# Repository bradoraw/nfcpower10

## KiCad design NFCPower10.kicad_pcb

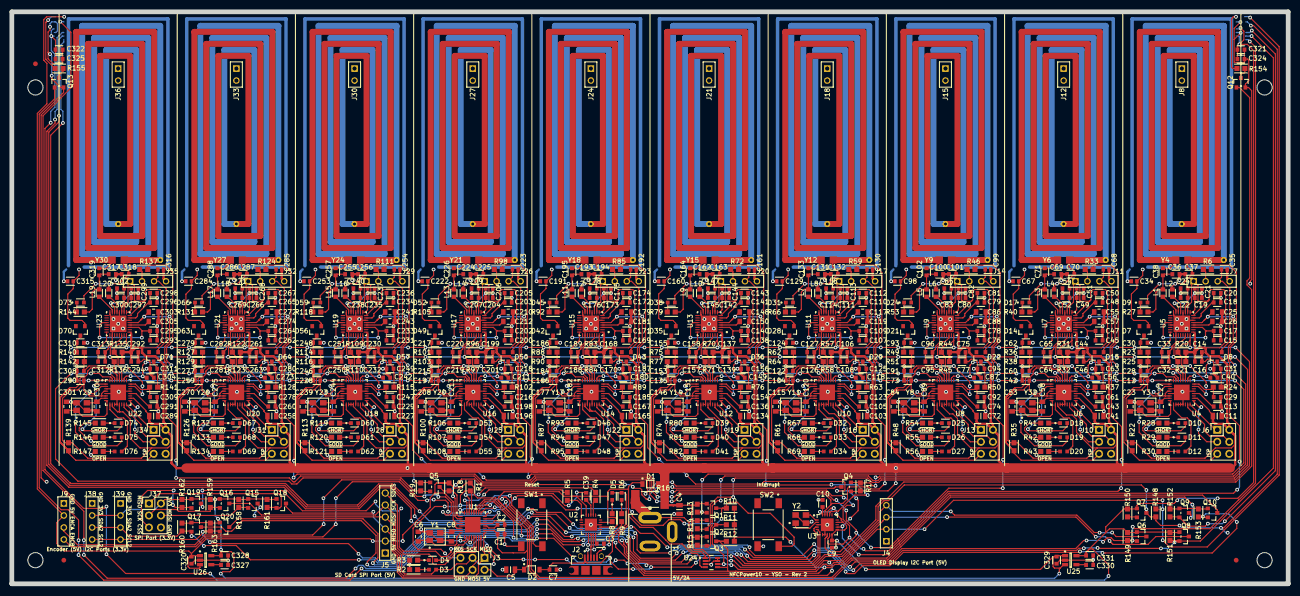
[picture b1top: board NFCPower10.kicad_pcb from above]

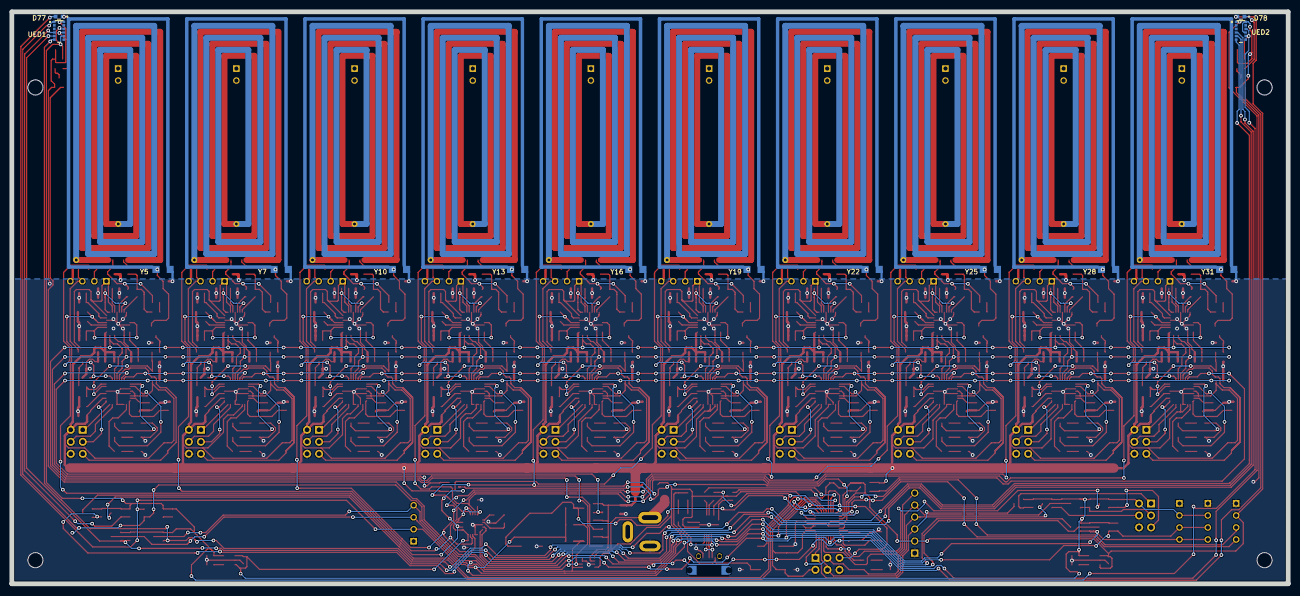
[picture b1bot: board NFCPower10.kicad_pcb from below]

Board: 2 copper layers, 270.0 x 121.0 mm, 666 parts (14 on the bottom side), 410 nets.

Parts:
C1, C2, C3, C7, C9, C10, C12, C13, C39, C42, C43, C73, C74, C104, C105, C135, C136, C166, C167, C197, C198, C228, C229, C259, C260, C290, C291, C321, C322, C327, C330: CC0603KPX7R9BB104; YAGEO-CC0603-0-0-0
C4, C5, C11, C41, C72, C103, C134, C165, C196, C227, C258, C289: CC0805ZKY5V6BB106; YAGEO-CC0805-0-0-0
C6, C8, C23, C25, C26, C27, C53, C55, C57, C58, C84, C86, C88, C89, C115, C117, C119, C120, C146, C148, C150, C151, C177, C179, C181, C182, C208, C210, C212, C213, C239, C241, C243, C244, C270, C272, C274, C275, C301, C303, C305, C306: CGA3E2C0G1H060D080AA; TDK-CGA3E-0.3-0.1-0-0-IPC_A
C14, C15, C18, C19, C22, C32, C44, C45, C48, C49, C52, C64, C75, C76, C79, C80, C83, C95, C106, C107, C110, C111, C114, C126, C137, C138, C141, C142, C145, C157, C168, C169, C172, C173, C176, C188, C199, C200, C203, C204, C207, C219, C230, C231, C234, C235, C238, C250, C261, C262, C265, C266, C269, C281, C292, C293, C296, C297, C300, C312, C320, C324, C325, C328, C329, C331: CC0603MRX5R5BB225; YAGEO-CC0603-0-0-0
C16, C17, C20, C21, C24, C33, C46, C47, C50, C51, C54, C65, C77, C78, C81, C82, C85, C96, C108, C109, C112, C113, C116, C127, C139, C140, C143, C144, C147, C158, C170, C171, C174, C175, C178, C189, C201, C202, C205, C206, C209, C220, C232, C233, C236, C237, C240, C251, C263, C264, C267, C268, C271, C282, C294, C295, C298, C299, C302, C313: CC0603KRX7R9BB103; YAGEO-CC0603-0-0-0
C28, C60, C91, C122, C153, C184, C215, C246, C277, C308: CC0603KRX7R6BB224; YAGEO-CC0603-0-0-0
C29, C40, C56, C61, C87, C92, C118, C123, C149, C154, C180, C185, C211, C216, C242, C247, C273, C278, C304, C309: CC0603KRX7R7BB105; YAGEO-CC0603-0-0-0
C30, C31, C36, C37, C62, C63, C69, C70, C93, C94, C100, C101, C124, C125, C131, C132, C155, C156, C162, C163, C186, C187, C193, C194, C217, C218, C224, C225, C248, C249, C255, C256, C279, C280, C286, C287, C310, C311, C317, C318: CC0603KRX7R9BB102; YAGEO-CC0603-0-0-0
C34, C35, C67, C68, C98, C99, C129, C130, C160, C161, C191, C192, C222, C223, C253, C254, C284, C285, C315, C316: C0603C209C5GACTU; KEMET-C0603C-CF-0-0-MFG
C38, C71, C102, C133, C164, C195, C226, C257, C288, C319: CC0603KRX7R9BB181; YAGEO-CC0603-0-0-0
D1, D2: BAT54T1G; On_Semiconductor-BAT54T1G-Manufacturer_Recommended
D3, D12, D20, D27, D34, D41, D48, D55, D62, D69, D76: LTST-C190TBKT; Vishay_Lite-On-LTST-C190TBKT-Manufacturer_Recommended
D4, D10, D18, D25, D32, D39, D46, D53, D60, D67, D74: LTST-C190KRKT; Lite-On-LTST-C190KRKT-MFG
D5, D11, D19, D26, D33, D40, D47, D54, D61, D68, D75, D77, D78: LTST-C190KGKT; Lite-On-LTST-C190KGKT-MFG
D6, D9, D17, D24, D31, D38, D45, D52, D59, D66, D73: LTST-C190KSKT; Lite-On-LTST-C190KSKT-MFG
D7, D8, D14, D15, D21, D22, D28, D29, D35, D36, D42, D43, D49, D50, D56, D57, D63, D64, D70, D71: BAS40-7-F; Diodes_Inc.-SOT23-01_2017-0-MFG
FID1, FID2, FID3: fiducial; Fiducial_1mm_Dia_2.54mm_Outer_CopperTop
J1: PJ-002AH; CUI_PJ-002AH
J2: 475890001; Molex-475890001-MFG
J3, J6, J10, J13, J16, J19, J22, J25, J28, J31, J34, J37: Conn_02x03_Odd_Even; Pin_Header_Straight_2x03_Pitch2.54mm
J4, J7, J9, J11, J14, J17, J20, J23, J26, J29, J32, J35, J38, J39: SSW-104-01-T-S; Samtec-SSW-104-01-T-S-Manufacturer_Recommended
J5: SSW-106-02-T-S; Samtec-SSW-106-02-T-S-Manufacturer_Recommended
J8, J12, J15, J18, J21, J24, J27, J30, J33, J36: SSW-102-01-T-S; Samtec-SSW-102-01-T-S-Manufacturer_Recommended
L1, L2, L3, L4, L5, L6, L7, L8, L9, L10, L11, L12, L13, L14, L15, L16, L17, L18, L19, L20: MLJ1608WR27JT000; INDC1608X95N
MT1, MT2, MT3, MT4: Mount Hole M3; MountingHole_3.2mm_M3
Q1, Q2, Q3, Q4, Q5, Q6, Q7, Q8, Q9, Q10, Q12, Q13, Q15, Q16, Q17, Q18, Q19, Q20: BSS138; ON_Semiconductor-318-08-01_2018-AS-MFG
R1, R10, R13, R14, R15, R17, R18, R19, R20, R21, R22, R23, R25, R31, R32, R35, R36, R38, R44, R45, R48, R49, R51, R57, R58, R61, R62, R64, R70, R71, R74, R75, R77, R83, R84, R87, R88, R90, R96, R97, R100, R101, R103, R109, R110, R113, R114, R116, R122, R123, R126, R127, R129, R135, R136, R139, R140, R142, R148, R150, R152, R153: RC0603FR-0710KL; Yageo-RC0603-0-0-IPC_A
R2, R3, R4, R5, R6, R8, R9, R11, R12, R24, R27, R28, R29, R30, R33, R37, R40, R41, R42, R43, R46, R50, R53, R54, R55, R56, R59, R63, R66, R67, R68, R69, R72, R76, R79, R80, R81, R82, R85, R89, R92, R93, R94, R95, R98, R102, R105, R106, R107, R108, R111, R115, R118, R119, R120, R121, R124, R128, R131, R132, R133, R134, R137, R141, R144, R145, R146, R147, R149, R151, R154, R155, R158, R159, R160, R161, R162, R163: RC0603FR-071K65L; Yageo-RC0603-0-0-IPC_A
R16: RL2512FK-070R1L; YAGEO-RL2512-02_2018-10-MFG
SW1, SW2: FSM2JSMAA; TE_Connectivity-FSM2JSMAA-MFG
U1, U4, U6, U8, U10, U12, U14, U16, U18, U20, U22: ATMEGA328P-MU; Microchip___Atmel-ATMEGA328P-MU-Level_A
U2: FT231XQ-R; FTDI-QFN-20-0-0-MFG
U3: Si5351A-B-GM; Silicon_Labs-Si5351A-B-GM-Level_A
U5, U7, U9, U11, U13, U15, U17, U19, U21, U23: ST25R3916-AQWT; STMicroelectronics-VFQFPN32-B04R-0-1-IPC_A
U24: INA219AIDCNR; Texas_Instruments-DCN0008A-0-0-MFG
U25: LP3985IM5X-2.8_NOPB; TI_National_Semiconductor-LP3985IM5X-2.8_NOPB-Level_A
U26: LP3985IM5X-3.3_NOPB; TI_National_Semiconductor-LP3985IM5X-3.3_NOPB-Level_A
UED1, UED2: VL6180XV0NR_1; STMicroelectronics-VL6180XV0NR_1-MFG
Y1, Y3, Y8, Y11, Y14, Y17, Y20, Y23, Y26, Y29, Y32: TSX-3225_16.0000MF09Z-AC3; Epson-TSX-3225_16.0000MF09Z-AC3-0
Y2: ABM8G-25.000MHz-B4Y-T; Abracon-ABM8G-25.000MHz-B4Y-T-0
Y4, Y6, Y9, Y12, Y15, Y18, Y21, Y24, Y27, Y30: Coil_49_18_6T_2Layer
Y5, Y7, Y10, Y13, Y16, Y19, Y22, Y25, Y28, Y31: Field_Sensor_54_22

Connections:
+5V: C1.1, C5.2, C320.1, D1.1, D2.1, D77.2, D78.2, J3.2, J4.2, J5.2, J9.2, R1.1, R10.1, R11.1, R12.1, R18.1, R148.1, U1.4, U1.6, U1.18, U2.12, U2.20, U24.4, U26.1, U26.3
+5VP: C4.2, C11.2, C12.1, C14.1, C16.1, C41.2, C42.1, C44.1, C46.1, C72.2, C73.1, C75.1, C77.1, C103.2, C104.1, C106.1, C108.1, C134.2, C135.1, C137.1, C139.1, C165.2, C166.1, C168.1, C170.1, C196.2, C197.1, C199.1, C201.1, C227.2, C228.1, C230.1, C232.1, C258.2, C259.1, C261.1, C263.1, C289.2, C290.1, C292.1, C294.1, D1.2, J6.2, J7.1, J10.2, J11.1, J13.2, J14.1, J16.2, J17.1, J19.2, J20.1, J22.2, J23.1, J25.2, J26.1, J28.2, J29.1, J31.2, J32.1, J34.2, J35.1, Q1.1, Q2.1, Q3.1, Q4.1, Q5.1, R13.1, R14.1, R15.1, R16.2, R17.1, R19.1, R20.2, R21.2, R22.2, R31.2, R32.2, R35.2, R44.2, R45.2, R48.2, R57.2, R58.2, R61.2, R70.2, R71.2, R74.2, R83.2, R84.2, R87.2, R96.2, R97.2, R100.2, R109.2, R110.2, R113.2, R122.2, R123.2, R126.2, R135.2, R136.2, R139.2, U4.4, U4.6, U4.18, U5.1, U5.8, U5.10, U6.4, U6.6, U6.10, U6.18, U7.1, U7.8, U7.10, U8.4, U8.6, U8.11, U8.18, U9.1, U9.8, U9.10, U10.4, U10.6, U10.10, U10.11, U10.18, U11.1, U11.8, U11.10, U12.4, U12.6, U12.12, U12.18, U13.1, U13.8, U13.10, U14.4, U14.6, U14.10, U14.12, U14.18, U15.1, U15.8, U15.10, U16.4, U16.6, U16.11, U16.12, U16.18, U17.1, U17.8, U17.10, U18.4, U18.6, U18.10, U18.11, U18.12, U18.18, U19.1, U19.8, U19.10, U20.4, U20.6, U20.13, U20.18, U21.1, U21.8, U21.10, U22.4, U22.6, U22.10, U22.13, U22.18, U23.1, U23.8, U23.10, U24.2
/CLK1: C25.1, C179.1, U3.12, U5.5, U15.5
/CLK2: C55.1, C210.1, U3.9, U7.5, U17.5
/CLK3: C86.1, C241.1, U3.8, U9.5, U19.5
/CLK4: C117.1, C272.1, U3.19, U11.5, U21.5
/CLK5: C148.1, C303.1, U3.17, U13.5, U23.5
/CSS: Q19.3, U1.13
/DEV1/2V8: C321.1, C322.1, C324.1, C325.1, C331.1, Q6.1, Q7.1, Q8.1, Q9.1, Q10.1, R149.1, R150.1, R151.1, R152.1, R153.1, U25.5, UED1.8, UED1.10, UED2.8, UED2.10
/DEV1/3V3: C9.1, C10.1, C328.1, C329.1, J37.2, J38.2, J39.2, Q15.1, Q16.1, Q17.1, Q18.1, Q19.1, Q20.1, R158.1, R159.1, R160.1, R161.1, R162.1, R163.1, U3.10, U3.11, U3.14, U3.18, U3.20, U25.1, U25.3, U26.5
/DEV1/CSS3: J37.5, Q19.2, R162.2
/DEV1/ENED12: Q9.2, R152.2, UED1.4
/DEV1/ENED22: Q10.2, R153.2, UED2.4
/DEV1/IED2: Q7.2, R150.2
/DEV1/MISO3: J37.1, Q18.2, R161.2
/DEV1/MOSI3: J37.4, Q15.2, R158.2
/DEV1/SCK3: J37.3, Q16.2, R159.2
/DEV1/SCL2: Q8.2, R151.2, UED1.5, UED2.5
/DEV1/SCL3: J38.4, J39.4, Q20.2, R163.2, U3.4
/DEV1/SDA2: Q6.2, R149.2, UED1.6, UED2.6
/DEV1/SDA3: J38.3, J39.3, Q17.2, R160.2, U3.5
/DTRD: C39.1, U2.18
/ENCA: J9.3, U1.23
/ENCB: J9.4, U1.24
/ENED1: Q9.3, U1.25
/ENED2: Q10.3, U1.26
/GRN: Q12.1, Q13.1, U1.10
/IED: Q7.3, R148.2, U1.12, UED1.1, UED2.1
/IRQ: Q1.3, R10.2, SW2.2, U1.32
/IRQP: Q1.2, R13.2, U4.32, U6.32, U8.32, U10.32, U12.32, U14.32, U16.32, U18.32, U20.32, U22.32
/MISO: J3.1, J5.3, Q18.3, U1.16
/MOSI: J3.4, J5.4, Q15.3, U1.15
/RED: D4.2, U1.11
/RES: C39.2, J3.5, R1.2, SW1.2, U1.29
/RX: R4.2, U1.30
/RXD: R5.1, U2.1
/RXLED#: R8.2, U2.14
/RXP: Q4.2, R17.2, U4.30
/RXT: Q5.3, R18.2, U1.1
/SCK: D3.1, J3.3, J5.5, Q16.3, U1.17
/SCL: J4.3, Q3.3, Q8.3, Q20.3, R12.2, U1.28, U24.5
/SCLP: Q3.2, R15.2, R21.1, R32.1, R45.1, R58.1, R71.1, R84.1, R97.1, R110.1, R123.1, R136.1, U4.28, U5.30, U6.28, U7.30, U8.28, U9.30, U10.28, U11.30, U12.28, U13.30, U14.28, U15.30, U16.28, U17.30, U18.28, U19.30, U20.28, U21.30, U22.28, U23.30
/SDA: J4.4, Q2.3, Q6.3, Q17.3, R11.2, U1.27, U24.6
/SDAP: Q2.2, R14.2, R20.1, R31.1, R44.1, R57.1, R70.1, R83.1, R96.1, R109.1, R122.1, R135.1, U4.27, U5.32, U6.27, U7.32, U8.27, U9.32, U10.27, U11.32, U12.27, U13.32, U14.27, U15.32, U16.27, U17.32, U18.27, U19.32, U20.27, U21.32, U22.27, U23.32
/SDCS: J5.6, U1.14
/TX: R5.2, U1.31
/TX1/AGDC: C32.1, C33.1, U5.24
/TX1/BLU: D12.1, U4.9
/TX1/GRN: D11.2, U4.2
/TX1/HSEN1: C34.1, D7.1, Y5.1
/TX1/HSEN2: C35.1, D8.1, J7.3
/TX1/LSEN2: J7.2, R6.1
/TX1/MISO: J6.1, U4.16
/TX1/MOSI: J6.4, U4.15
/TX1/RED: D10.2, U4.1
/TX1/RES: J6.5, R22.1, U4.29
/TX1/RF1: C37.2, D9.2, L2.2, Y4.2
/TX1/RF2: C36.1, C38.1, L1.2, R27.2
/TX1/RFO1: L2.1, U5.13
/TX1/RFO2: L1.1, U5.15
/TX1/SCK: J6.3, U4.17
/TX1/VDD_A: C18.1, C20.1, U5.7
/TX1/VDD_AM: C22.1, C24.1, U5.11
/TX1/VDD_D: C15.1, C17.1, U5.3, U5.20
/TX1/VDD_RF: C19.1, C21.1, U5.9, U5.14
/TX1/VDET1: C28.1, R23.1, R25.1, U4.23
/TX1/VDET2: C29.1, R24.1, U4.24
/TX1/VPD2: C40.1, R6.2, U4.26
/TX2/AGDC: C64.1, C65.1, U7.24
/TX2/BLU: D20.1, U6.9
/TX2/GRN: D19.2, U6.2
/TX2/HSEN1: C67.1, D14.1, Y7.1
/TX2/HSEN2: C68.1, D15.1, J11.3
/TX2/LSEN2: J11.2, R33.1
/TX2/MISO: J10.1, U6.16
/TX2/MOSI: J10.4, U6.15
/TX2/RED: D18.2, U6.1
/TX2/RES: J10.5, R35.1, U6.29
/TX2/RF1: C70.2, D17.2, L4.2, Y6.2
/TX2/RF2: C69.1, C71.1, L3.2, R40.2
/TX2/RFO1: L4.1, U7.13
/TX2/RFO2: L3.1, U7.15
/TX2/RX: U4.31, U6.30
/TX2/SCK: J10.3, U6.17
/TX2/VDD_A: C48.1, C50.1, U7.7
/TX2/VDD_AM: C52.1, C54.1, U7.11
/TX2/VDD_D: C45.1, C47.1, U7.3, U7.20
/TX2/VDD_RF: C49.1, C51.1, U7.9, U7.14
/TX2/VDET1: C60.1, R36.1, R38.1, U6.23
/TX2/VDET2: C61.1, R37.1, U6.24
/TX2/VPD2: C56.1, R33.2, U6.26
/TX3/AGDC: C95.1, C96.1, U9.24
/TX3/BLU: D27.1, U8.9
/TX3/GRN: D26.2, U8.2
/TX3/HSEN1: C98.1, D21.1, Y10.1
/TX3/HSEN2: C99.1, D22.1, J14.3
/TX3/LSEN2: J14.2, R46.1
/TX3/MISO: J13.1, U8.16
/TX3/MOSI: J13.4, U8.15
/TX3/RED: D25.2, U8.1
/TX3/RES: J13.5, R48.1, U8.29
/TX3/RF1: C101.2, D24.2, L6.2, Y9.2
/TX3/RF2: C100.1, C102.1, L5.2, R53.2
/TX3/RFO1: L6.1, U9.13
/TX3/RFO2: L5.1, U9.15
/TX3/RX: U6.31, U8.30
/TX3/SCK: J13.3, U8.17
/TX3/VDD_A: C79.1, C81.1, U9.7
/TX3/VDD_AM: C83.1, C85.1, U9.11
/TX3/VDD_D: C76.1, C78.1, U9.3, U9.20
/TX3/VDD_RF: C80.1, C82.1, U9.9, U9.14
/TX3/VDET1: C91.1, R49.1, R51.1, U8.23
/TX3/VDET2: C92.1, R50.1, U8.24
/TX3/VPD2: C87.1, R46.2, U8.26
/TX4/AGDC: C126.1, C127.1, U11.24
/TX4/BLU: D34.1, U10.9
/TX4/GRN: D33.2, U10.2
/TX4/HSEN1: C129.1, D28.1, Y13.1
/TX4/HSEN2: C130.1, D29.1, J17.3
/TX4/LSEN2: J17.2, R59.1
/TX4/MISO: J16.1, U10.16
/TX4/MOSI: J16.4, U10.15
/TX4/RED: D32.2, U10.1
/TX4/RES: J16.5, R61.1, U10.29
/TX4/RF1: C132.2, D31.2, L8.2, Y12.2
/TX4/RF2: C131.1, C133.1, L7.2, R66.2
/TX4/RFO1: L8.1, U11.13
/TX4/RFO2: L7.1, U11.15
/TX4/RX: U8.31, U10.30
/TX4/SCK: J16.3, U10.17
/TX4/VDD_A: C110.1, C112.1, U11.7
/TX4/VDD_AM: C114.1, C116.1, U11.11
/TX4/VDD_D: C107.1, C109.1, U11.3, U11.20
/TX4/VDD_RF: C111.1, C113.1, U11.9, U11.14
/TX4/VDET1: C122.1, R62.1, R64.1, U10.23
/TX4/VDET2: C123.1, R63.1, U10.24
/TX4/VPD2: C118.1, R59.2, U10.26
/TX5/AGDC: C157.1, C158.1, U13.24
/TX5/BLU: D41.1, U12.9
/TX5/GRN: D40.2, U12.2
/TX5/HSEN1: C160.1, D35.1, Y16.1
/TX5/HSEN2: C161.1, D36.1, J20.3
/TX5/LSEN2: J20.2, R72.1
/TX5/MISO: J19.1, U12.16
/TX5/MOSI: J19.4, U12.15
/TX5/RED: D39.2, U12.1
/TX5/RES: J19.5, R74.1, U12.29
/TX5/RF1: C163.2, D38.2, L10.2, Y15.2
/TX5/RF2: C162.1, C164.1, L9.2, R79.2
/TX5/RFO1: L10.1, U13.13
/TX5/RFO2: L9.1, U13.15
/TX5/RX: U10.31, U12.30
/TX5/SCK: J19.3, U12.17
/TX5/VDD_A: C141.1, C143.1, U13.7
/TX5/VDD_AM: C145.1, C147.1, U13.11
/TX5/VDD_D: C138.1, C140.1, U13.3, U13.20
/TX5/VDD_RF: C142.1, C144.1, U13.9, U13.14
/TX5/VDET1: C153.1, R75.1, R77.1, U12.23
/TX5/VDET2: C154.1, R76.1, U12.24
/TX5/VPD2: C149.1, R72.2, U12.26
/TX6/AGDC: C188.1, C189.1, U15.24
/TX6/BLU: D48.1, U14.9
/TX6/GRN: D47.2, U14.2
/TX6/HSEN1: C191.1, D42.1, Y19.1
/TX6/HSEN2: C192.1, D43.1, J23.3
/TX6/LSEN2: J23.2, R85.1
/TX6/MISO: J22.1, U14.16
/TX6/MOSI: J22.4, U14.15
/TX6/RED: D46.2, U14.1
/TX6/RES: J22.5, R87.1, U14.29
/TX6/RF1: C194.2, D45.2, L12.2, Y18.2
/TX6/RF2: C193.1, C195.1, L11.2, R92.2
/TX6/RFO1: L12.1, U15.13
/TX6/RFO2: L11.1, U15.15
/TX6/RX: U12.31, U14.30
/TX6/SCK: J22.3, U14.17
/TX6/VDD_A: C172.1, C174.1, U15.7
/TX6/VDD_AM: C176.1, C178.1, U15.11
/TX6/VDD_D: C169.1, C171.1, U15.3, U15.20
/TX6/VDD_RF: C173.1, C175.1, U15.9, U15.14
/TX6/VDET1: C184.1, R88.1, R90.1, U14.23
/TX6/VDET2: C185.1, R89.1, U14.24
/TX6/VPD2: C180.1, R85.2, U14.26
/TX7/AGDC: C219.1, C220.1, U17.24
/TX7/BLU: D55.1, U16.9
/TX7/GRN: D54.2, U16.2
/TX7/HSEN1: C222.1, D49.1, Y22.1
/TX7/HSEN2: C223.1, D50.1, J26.3
/TX7/LSEN2: J26.2, R98.1
/TX7/MISO: J25.1, U16.16
/TX7/MOSI: J25.4, U16.15
/TX7/RED: D53.2, U16.1
/TX7/RES: J25.5, R100.1, U16.29
/TX7/RF1: C225.2, D52.2, L14.2, Y21.2
/TX7/RF2: C224.1, C226.1, L13.2, R105.2
/TX7/RFO1: L14.1, U17.13
/TX7/RFO2: L13.1, U17.15
/TX7/RX: U14.31, U16.30
/TX7/SCK: J25.3, U16.17
/TX7/VDD_A: C203.1, C205.1, U17.7
/TX7/VDD_AM: C207.1, C209.1, U17.11
/TX7/VDD_D: C200.1, C202.1, U17.3, U17.20
/TX7/VDD_RF: C204.1, C206.1, U17.9, U17.14
/TX7/VDET1: C215.1, R101.1, R103.1, U16.23
/TX7/VDET2: C216.1, R102.1, U16.24
/TX7/VPD2: C211.1, R98.2, U16.26
/TX8/AGDC: C250.1, C251.1, U19.24
/TX8/BLU: D62.1, U18.9
/TX8/GRN: D61.2, U18.2
/TX8/HSEN1: C253.1, D56.1, Y25.1
/TX8/HSEN2: C254.1, D57.1, J29.3
/TX8/LSEN2: J29.2, R111.1
/TX8/MISO: J28.1, U18.16
/TX8/MOSI: J28.4, U18.15
/TX8/RED: D60.2, U18.1
/TX8/RES: J28.5, R113.1, U18.29
/TX8/RF1: C256.2, D59.2, L16.2, Y24.2
/TX8/RF2: C255.1, C257.1, L15.2, R118.2
/TX8/RFO1: L16.1, U19.13
/TX8/RFO2: L15.1, U19.15
/TX8/RX: U16.31, U18.30
/TX8/SCK: J28.3, U18.17
/TX8/VDD_A: C234.1, C236.1, U19.7
/TX8/VDD_AM: C238.1, C240.1, U19.11
/TX8/VDD_D: C231.1, C233.1, U19.3, U19.20
/TX8/VDD_RF: C235.1, C237.1, U19.9, U19.14
/TX8/VDET1: C246.1, R114.1, R116.1, U18.23
/TX8/VDET2: C247.1, R115.1, U18.24
/TX8/VPD2: C242.1, R111.2, U18.26
/TX9/AGDC: C281.1, C282.1, U21.24
/TX9/BLU: D69.1, U20.9
/TX9/GRN: D68.2, U20.2
/TX9/HSEN1: C284.1, D63.1, Y28.1
/TX9/HSEN2: C285.1, D64.1, J32.3
/TX9/LSEN2: J32.2, R124.1
/TX9/MISO: J31.1, U20.16
/TX9/MOSI: J31.4, U20.15
/TX9/RED: D67.2, U20.1
/TX9/RES: J31.5, R126.1, U20.29
/TX9/RF1: C287.2, D66.2, L18.2, Y27.2
/TX9/RF2: C286.1, C288.1, L17.2, R131.2
/TX9/RFO1: L18.1, U21.13
/TX9/RFO2: L17.1, U21.15
/TX9/RX: U18.31, U20.30
/TX9/SCK: J31.3, U20.17
/TX9/VDD_A: C265.1, C267.1, U21.7
/TX9/VDD_AM: C269.1, C271.1, U21.11
/TX9/VDD_D: C262.1, C264.1, U21.3, U21.20
/TX9/VDD_RF: C266.1, C268.1, U21.9, U21.14
/TX9/VDET1: C277.1, R127.1, R129.1, U20.23
/TX9/VDET2: C278.1, R128.1, U20.24
/TX9/VPD2: C273.1, R124.2, U20.26
/TX10/AGDC: C312.1, C313.1, U23.24
/TX10/BLU: D76.1, U22.9
/TX10/GRN: D75.2, U22.2
/TX10/HSEN1: C315.1, D70.1, Y31.1
/TX10/HSEN2: C316.1, D71.1, J35.3
/TX10/LSEN2: J35.2, R137.1
/TX10/MISO: J34.1, U22.16
/TX10/MOSI: J34.4, U22.15
/TX10/RED: D74.2, U22.1
/TX10/RES: J34.5, R139.1, U22.29
/TX10/RF1: C318.2, D73.2, L20.2, Y30.2
/TX10/RF2: C317.1, C319.1, L19.2, R144.2
/TX10/RFO1: L20.1, U23.13
/TX10/RFO2: L19.1, U23.15
/TX10/RX: U20.31, U22.30
/TX10/SCK: J34.3, U22.17
/TX10/VDD_A: C296.1, C298.1, U23.7
/TX10/VDD_AM: C300.1, C302.1, U23.11
/TX10/VDD_D: C293.1, C295.1, U23.3, U23.20
/TX10/VDD_RF: C297.1, C299.1, U23.9, U23.14
/TX10/VDET1: C308.1, R140.1, R142.1, U22.23
/TX10/VDET2: C309.1, R141.1, U22.24
/TX10/VPD2: C304.1, R137.2, U22.26
/TXD: R4.1, U2.17
/TXLED#: R9.2, U2.7
/TXP: Q5.2, R19.2, U22.31
/TXT: Q4.3, U1.2
/VIN: J1.1, R16.1, U24.1
GND: C1.2, C2.2, C3.2, C4.1, C5.1, C6.2, C7.2, C8.2, C9.2, C10.2, C11.1, C12.2, C13.2, C14.2, C15.2, C16.2, C17.2, C18.2, C19.2, C20.2, C21.2, C22.2, C23.2, C24.2, C25.2, C26.2, C27.2, C28.2, C29.2, C30.2, C31.2, C32.2, C33.2, C34.2, C35.2, C36.2, C37.1, C40.2, C41.1, C42.2, C43.2, C44.2, C45.2, C46.2, C47.2, C48.2, C49.2, C50.2, C51.2, C52.2, C53.2, C54.2, C55.2, C56.2, C57.2, C58.2, C60.2, C61.2, C62.2, C63.2, C64.2, C65.2, C67.2, C68.2, C69.2, C70.1, C72.1, C73.2, C74.2, C75.2, C76.2, C77.2, C78.2, C79.2, C80.2, C81.2, C82.2, C83.2, C84.2, C85.2, C86.2, C87.2, C88.2, C89.2, C91.2, C92.2, C93.2, C94.2, C95.2, C96.2, C98.2, C99.2, C100.2, C101.1, C103.1, C104.2, C105.2, C106.2, C107.2, C108.2, C109.2, C110.2, C111.2, C112.2, C113.2, C114.2, C115.2, C116.2, C117.2, C118.2, C119.2, C120.2, C122.2, C123.2, C124.2, C125.2, C126.2, C127.2, C129.2, C130.2, C131.2, C132.1, C134.1, C135.2, C136.2, C137.2, C138.2, C139.2, C140.2, C141.2, C142.2, C143.2, C144.2, C145.2, C146.2, C147.2, C148.2, C149.2, C150.2, C151.2, C153.2, C154.2, C155.2, C156.2, C157.2, C158.2, C160.2, C161.2, C162.2, C163.1, C165.1, C166.2, C167.2, C168.2, C169.2, C170.2, C171.2, C172.2, C173.2, C174.2, C175.2, C176.2, C177.2, C178.2, C179.2, C180.2, C181.2, C182.2, C184.2, C185.2, C186.2, C187.2, C188.2, C189.2, C191.2, C192.2, C193.2, C194.1, C196.1, C197.2, C198.2, C199.2, C200.2, C201.2, C202.2, C203.2, C204.2, C205.2, C206.2, C207.2, C208.2, C209.2, C210.2, C211.2, C212.2, C213.2, C215.2, C216.2, C217.2, C218.2, C219.2, C220.2, C222.2, C223.2, C224.2, C225.1, C227.1, C228.2, C229.2, C230.2, C231.2, C232.2, C233.2, C234.2, C235.2, C236.2, C237.2, C238.2, C239.2, C240.2, C241.2, C242.2, C243.2, C244.2, C246.2, C247.2, C248.2, C249.2, C250.2, C251.2, C253.2, C254.2, C255.2, C256.1, C258.1, C259.2, C260.2, C261.2, C262.2, C263.2, C264.2, C265.2, C266.2, C267.2, C268.2, C269.2, C270.2, C271.2, C272.2, C273.2, C274.2, C275.2, C277.2, C278.2, C279.2, C280.2, C281.2, C282.2, C284.2, C285.2, C286.2, C287.1, C289.1, C290.2, C291.2, C292.2, C293.2, C294.2, C295.2, C296.2, C297.2, C298.2, C299.2, C300.2, C301.2, C302.2, C303.2, C304.2, C305.2, C306.2, C308.2, C309.2, C310.2, C311.2, C312.2, C313.2, C315.2, C316.2, C317.2, C318.1, C320.2, C321.2, C322.2, C324.2, C325.2, C327.2, C328.2, C329.2, C330.2, C331.2, J1.2, J2.5, J3.6, J4.1, J5.1, J6.6, J7.4, J9.1, J10.6, J11.4, J13.6, J14.4, J16.6, J17.4, J19.6, J20.4, J22.6, J23.4, J25.6, J26.4, J28.6, J29.4, J31.6, J32.4, J34.6, J35.4, J37.6, J38.1, J39.1, Q12.2, Q13.2, R2.2, R3.2, R25.2, R28.2, R29.2, R30.2, R38.2, R41.2, R42.2, R43.2, R51.2, R54.2, R55.2, R56.2, R64.2, R67.2, R68.2, R69.2, R77.2, R80.2, R81.2, R82.2, R90.2, R93.2, R94.2, R95.2, R103.2, R106.2, R107.2, R108.2, R116.2, R119.2, R120.2, R121.2, R129.2, R132.2, R133.2, R134.2, R142.2, R145.2, R146.2, R147.2, SW1.4, SW2.4, U1.3, U1.5, U1.21, U1.33, U2.3, U2.13, U2.21, U3.3, U3.6, U3.7, U3.21, U4.3, U4.5, U4.10, U4.11, U4.12, U4.13, U4.21, U4.33, U5.6, U5.12, U5.16, U5.21, U5.26, U5.33, U6.3, U6.5, U6.11, U6.12, U6.13, U6.21, U6.33, U7.6, U7.12, U7.16, U7.21, U7.26, U7.33, U8.3, U8.5, U8.10, U8.12, U8.13, U8.21, U8.33, U9.6, U9.12, U9.16, U9.21, U9.26, U9.33, U10.3, U10.5, U10.12, U10.13, U10.21, U10.33, U11.6, U11.12, U11.16, U11.21, U11.26, U11.33, U12.3, U12.5, U12.10, U12.11, U12.13, U12.21, U12.33, U13.6, U13.12, U13.16, U13.21, U13.26, U13.33, U14.3, U14.5, U14.11, U14.13, U14.21, U14.33, U15.6, U15.12, U15.16, U15.21, U15.26, U15.33, U16.3, U16.5, U16.10, U16.13, U16.21, U16.33, U17.6, U17.12, U17.16, U17.21, U17.26, U17.33, U18.3, U18.5, U18.13, U18.21, U18.33, U19.6, U19.12, U19.16, U19.21, U19.26, U19.33, U20.3, U20.5, U20.10, U20.11, U20.12, U20.21, U20.33, U21.6, U21.12, U21.16, U21.21, U21.26, U21.33, U22.3, U22.5, U22.11, U22.12, U22.21, U22.33, U23.6, U23.12, U23.16, U23.21, U23.26, U23.33, U24.3, U24.7, U24.8, U25.2, U26.2, UED1.9, UED1.12, UED2.9, UED2.12, Y1.2, Y1.4, Y2.2, Y2.4, Y3.2, Y3.4, Y5.2, Y7.2, Y8.2, Y8.4, Y10.2, Y11.2, Y11.4, Y13.2, Y14.2, Y14.4, Y16.2, Y17.2, Y17.4, Y19.2, Y20.2, Y20.4, Y22.2, Y23.2, Y23.4, Y25.2, Y26.2, Y26.4, Y28.2, Y29.2, Y29.4, Y31.2, Y32.2, Y32.4
unnamed: C2.1, U1.20
unnamed: C3.1, U2.10
unnamed: C6.1, U1.8, Y1.1
unnamed: C8.1, U1.7, Y1.3
unnamed: C13.1, U4.20
unnamed: C23.1, U4.8, Y3.1
unnamed: C26.1, U5.4
unnamed: C27.1, U4.7, Y3.3
unnamed: C30.1, D7.3, R23.2
unnamed: C31.1, D8.3, R24.2
unnamed: C38.2, Y4.1
unnamed: C43.1, U6.20
unnamed: C53.1, U6.8, Y32.1
unnamed: C57.1, U7.4
unnamed: C58.1, U6.7, Y32.3
unnamed: C62.1, D14.3, R36.2
unnamed: C63.1, D15.3, R37.2
unnamed: C71.2, Y6.1
unnamed: C74.1, U8.20
unnamed: C84.1, U8.8, Y8.1
unnamed: C88.1, U9.4
unnamed: C89.1, U8.7, Y8.3
unnamed: C93.1, D21.3, R49.2
unnamed: C94.1, D22.3, R50.2
unnamed: C102.2, Y9.1
unnamed: C105.1, U10.20
unnamed: C115.1, U10.8, Y11.1
unnamed: C119.1, U11.4
unnamed: C120.1, U10.7, Y11.3
unnamed: C124.1, D28.3, R62.2
unnamed: C125.1, D29.3, R63.2
unnamed: C133.2, Y12.1
unnamed: C136.1, U12.20
unnamed: C146.1, U12.8, Y14.1
unnamed: C150.1, U13.4
unnamed: C151.1, U12.7, Y14.3
unnamed: C155.1, D35.3, R75.2
unnamed: C156.1, D36.3, R76.2
unnamed: C164.2, Y15.1
unnamed: C167.1, U14.20
unnamed: C177.1, U14.8, Y17.1
unnamed: C181.1, U15.4
unnamed: C182.1, U14.7, Y17.3
unnamed: C186.1, D42.3, R88.2
unnamed: C187.1, D43.3, R89.2
unnamed: C195.2, Y18.1
unnamed: C198.1, U16.20
unnamed: C208.1, U16.8, Y20.1
unnamed: C212.1, U17.4
unnamed: C213.1, U16.7, Y20.3
unnamed: C217.1, D49.3, R101.2
unnamed: C218.1, D50.3, R102.2
unnamed: C226.2, Y21.1
unnamed: C229.1, U18.20
unnamed: C239.1, U18.8, Y23.1
unnamed: C243.1, U19.4
unnamed: C244.1, U18.7, Y23.3
unnamed: C248.1, D56.3, R114.2
unnamed: C249.1, D57.3, R115.2
unnamed: C257.2, Y24.1
unnamed: C260.1, U20.20
unnamed: C270.1, U20.8, Y26.1
unnamed: C274.1, U21.4
unnamed: C275.1, U20.7, Y26.3
unnamed: C279.1, D63.3, R127.2
unnamed: C280.1, D64.3, R128.2
unnamed: C288.2, Y27.1
unnamed: C291.1, U22.20
unnamed: C301.1, U22.8, Y29.1
unnamed: C305.1, U23.4
unnamed: C306.1, U22.7, Y29.3
unnamed: C310.1, D70.3, R140.2
unnamed: C311.1, D71.3, R141.2
unnamed: C319.2, Y30.1
unnamed: C327.1, U26.4
unnamed: C330.1, U25.4
unnamed: D3.2, R2.1
unnamed: D4.1, R3.1
unnamed: D5.1, R8.1
unnamed: D6.1, R9.1
unnamed: D9.1, R27.1
unnamed: D10.1, R28.1
unnamed: D11.1, R29.1
unnamed: D12.2, R30.1
unnamed: D17.1, R40.1
unnamed: D18.1, R41.1
unnamed: D19.1, R42.1
unnamed: D20.2, R43.1
unnamed: D24.1, R53.1
unnamed: D25.1, R54.1
unnamed: D26.1, R55.1
unnamed: D27.2, R56.1
unnamed: D31.1, R66.1
unnamed: D32.1, R67.1
unnamed: D33.1, R68.1
unnamed: D34.2, R69.1
unnamed: D38.1, R79.1
unnamed: D39.1, R80.1
unnamed: D40.1, R81.1
unnamed: D41.2, R82.1
unnamed: D45.1, R92.1
unnamed: D46.1, R93.1
unnamed: D47.1, R94.1
unnamed: D48.2, R95.1
unnamed: D52.1, R105.1
unnamed: D53.1, R106.1
unnamed: D54.1, R107.1
unnamed: D55.2, R108.1
unnamed: D59.1, R118.1
unnamed: D60.1, R119.1
unnamed: D61.1, R120.1
unnamed: D62.2, R121.1
unnamed: D66.1, R131.1
unnamed: D67.1, R132.1
unnamed: D68.1, R133.1
unnamed: D69.2, R134.1
unnamed: D73.1, R144.1
unnamed: D74.1, R145.1
unnamed: D75.1, R146.1
unnamed: D76.2, R147.1
unnamed: D77.1, R154.1
unnamed: D78.1, R155.1
unnamed: J2.2, U2.9
unnamed: J2.3, U2.8
unnamed: Q12.3, R154.2
unnamed: Q13.3, R155.2
unnamed: U3.1, Y2.3
unnamed: U3.2, Y2.1
VBUS: C7.1, D2.2, D5.2, D6.2, J2.1

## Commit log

2020-11-25 add si5351. and separate power side logic SCLP SDAP and IRQP when power not applied to +5VP.
2020-11-26 initial placement
2020-11-27 initial routing
2020-11-27 continue routing. add INA219 to monitor +5VP rail.
2020-11-27 route complete
2020-11-27 manufacturing files
2020-12-10 create initial firmware
2020-12-16 fix issue with transmitter updatStat. fix some issue on host with Si5351 clock gen. use modified library for 8 clock outputs.
2020-12-17 testing
2020-12-17 add digital low pass filter
2021-01-27 rev 2
2021-01-27 remove
2021-02-15 add trigger signal. print min or max to serial port
2021-02-17 trigger based on field not working well. instead use photo gate driving IRQ to create trigger. after trigger detect print Trig to trigger camera. then read 10 field values and print Fields followed b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
